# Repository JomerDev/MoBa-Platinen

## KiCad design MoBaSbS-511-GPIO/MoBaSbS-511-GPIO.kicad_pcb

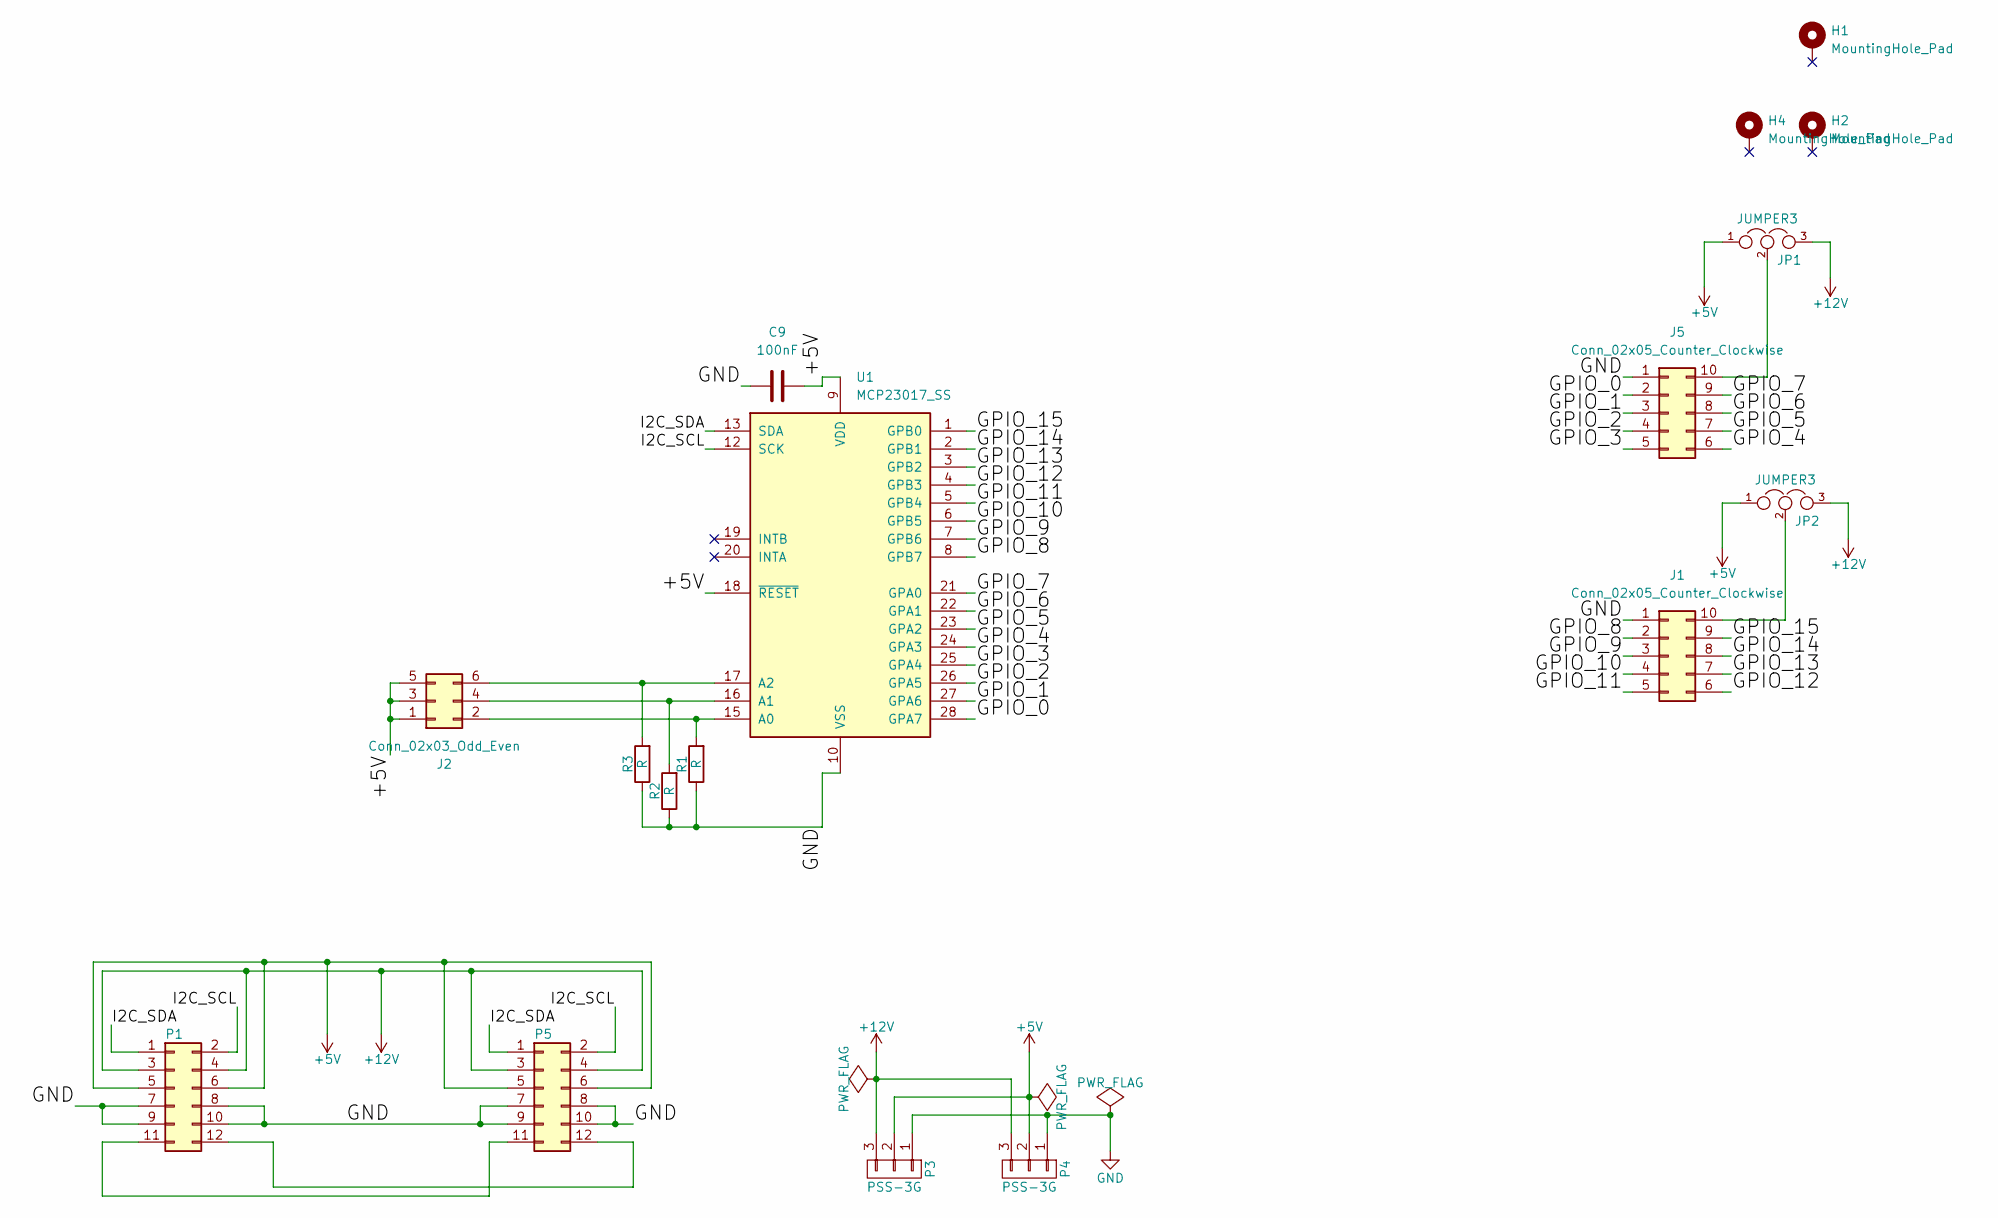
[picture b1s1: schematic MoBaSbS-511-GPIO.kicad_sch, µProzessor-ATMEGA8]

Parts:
C9: 100nF; C_0603_1608Metric
H1, H2, H4: MountingHole_Pad; MountingHole_2.7mm_M2.5_DIN965_Pad
J1, J5: Conn_02x05_Counter_Clockwise; IDC-Header_2x05_P2.54mm_Vertical
J2: Conn_02x03_Odd_Even; PinHeader_2x03_P2.54mm_Vertical
JP1, JP2: JUMPER3; Pin_Header_Straight_1x03
P1: 2x5_Buchse; PinSocket_2x06_P2.54mm_Horizontal
P3, P4: PSS-3G; PSS254-3G
P5: 2x5_Buchse; PinHeader_2x06_P2.54mm_Horizontal
R1, R2, R3: R; R_0603_1608Metric_Pad0.98x0.95mm_HandSolder
U1: MCP23017_SS; SSOP-28_5.3x10.2mm_P0.65mm

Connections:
+5V: C9.2, J2.1, J2.3, J2.5, JP1.1, JP2.1, P1.5, P1.6, P3.2, P4.2, P5.5, P5.6, U1.9 (VDD), U1.18 (~RESET)
+12V: JP1.3, JP2.3, P1.3, P1.4, P3.3, P4.3, P5.3, P5.4
/GPIO_0: J5.2, U1.28 (GPA7)
/GPIO_1: J5.3, U1.27 (GPA6)
/GPIO_2: J5.4, U1.26 (GPA5)
/GPIO_3: J5.5, U1.25 (GPA4)
/GPIO_4: J5.6, U1.24 (GPA3)
/GPIO_5: J5.7, U1.23 (GPA2)
/GPIO_6: J5.8, U1.22 (GPA1)
/GPIO_7: J5.9, U1.21 (GPA0)
/GPIO_8: J1.2, U1.8 (GPB7)
/GPIO_9: J1.3, U1.7 (GPB6)
/GPIO_10: J1.4, U1.6 (GPB5)
/GPIO_11: J1.5, U1.5 (GPB4)
/GPIO_12: J1.6, U1.4 (GPB3)
/GPIO_13: J1.7, U1.3 (GPB2)
/GPIO_14: J1.8, U1.2 (GPB1)
/GPIO_15: J1.9, U1.1 (GPB0)
/I2C_SCL: P1.2, P5.2, U1.12 (SCK)
/I2C_SDA: P1.1, P5.1, U1.13 (SDA)
GND: C9.1, J1.1, J5.1, P1.7, P1.8, P1.9, P1.10, P3.1, P4.1, P5.7, P5.8, P5.9, P5.10, R1.1, R2.1, R3.1, U1.10 (VSS)
unnamed: J1.10, JP2.2
unnamed: J2.2, R1.2, U1.15 (A0)
unnamed: J2.4, R2.2, U1.16 (A1)
unnamed: J2.6, R3.2, U1.17 (A2)
unnamed: J5.10, JP1.2
unnamed: P1.11, P5.11
unnamed: P1.12, P5.12

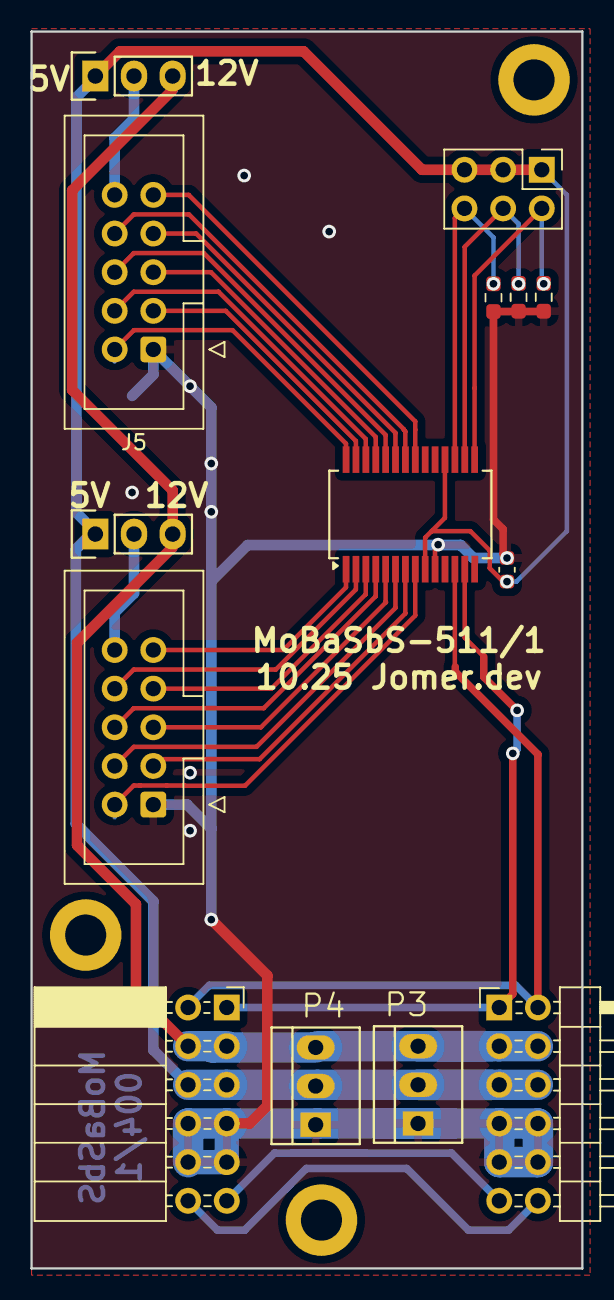
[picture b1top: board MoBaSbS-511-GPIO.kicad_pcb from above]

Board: 2 copper layers, 36.2 x 81.3 mm, 17 parts (0 on the bottom side), 28 nets.

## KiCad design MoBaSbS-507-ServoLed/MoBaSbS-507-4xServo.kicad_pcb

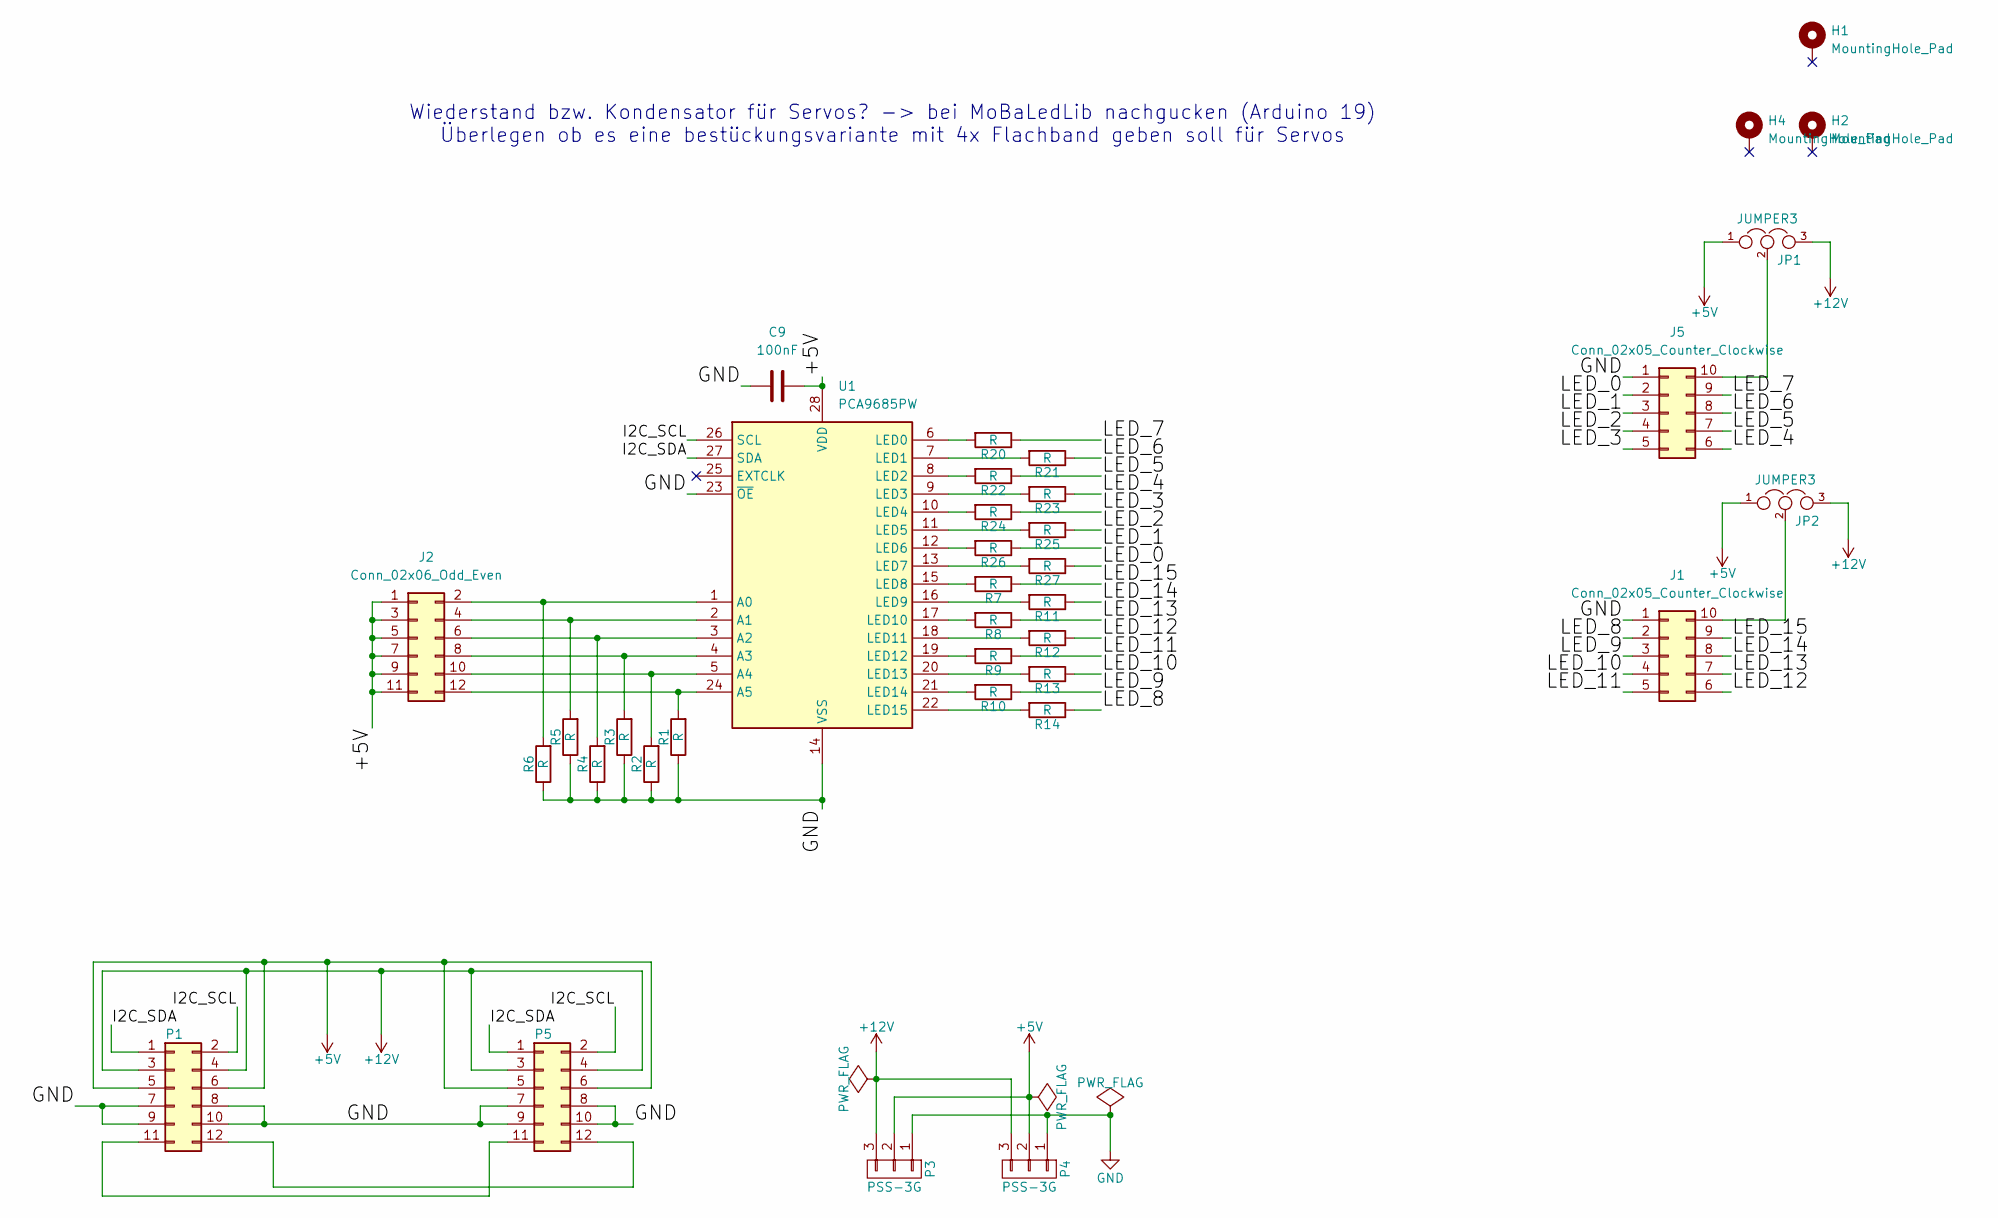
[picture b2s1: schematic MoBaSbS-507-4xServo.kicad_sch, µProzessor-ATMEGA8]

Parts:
C9: 100nF; C_0603_1608Metric
H1, H2, H4: MountingHole_Pad; MountingHole_2.7mm_M2.5_DIN965_Pad
J1, J5: Conn_02x05_Counter_Clockwise; IDC-Header_2x05_P2.54mm_Vertical
J2: Conn_02x06_Odd_Even; PinHeader_2x06_P2.54mm_Vertical
JP1, JP2: JUMPER3; Pin_Header_Straight_1x03
P1: 2x5_Buchse; PinSocket_2x06_P2.54mm_Horizontal
P3, P4: PSS-3G; PSS254-3G
P5: 2x5_Buchse; PinHeader_2x06_P2.54mm_Horizontal
R1, R2, R3, R4, R5, R6: R; R_0603_1608Metric_Pad0.98x0.95mm_HandSolder
R7, R8, R9, R10, R11, R12, R13, R14, R20, R21, R22, R23, R24, R25, R26, R27: R; R_1206_3216Metric_Pad1.30x1.75mm_HandSolder
U1: PCA9685PW; TSSOP-28_4.4x9.7mm_P0.65mm

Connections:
+5V: C9.2, J2.1, J2.3, J2.5, J2.7, J2.9, J2.11, JP1.1, JP2.1, P1.5, P1.6, P3.2, P4.2, P5.5, P5.6, U1.28 (VDD)
+12V: JP1.3, JP2.3, P1.3, P1.4, P3.3, P4.3, P5.3, P5.4
/I2C_SCL: P1.2, P5.2, U1.26 (SCL)
/I2C_SDA: P1.1, P5.1, U1.27 (SDA)
/LED_0: J5.2, R27.1
/LED_1: J5.3, R26.1
/LED_2: J5.4, R25.1
/LED_3: J5.5, R24.1
/LED_4: J5.6, R23.1
/LED_5: J5.7, R22.1
/LED_6: J5.8, R21.1
/LED_7: J5.9, R20.1
/LED_8: J1.2, R14.1
/LED_9: J1.3, R10.1
/LED_10: J1.4, R13.1
/LED_11: J1.5, R9.1
/LED_12: J1.6, R12.1
/LED_13: J1.7, R8.1
/LED_14: J1.8, R11.1
/LED_15: J1.9, R7.1
GND: C9.1, J1.1, J5.1, P1.7, P1.8, P1.9, P1.10, P3.1, P4.1, P5.7, P5.8, P5.9, P5.10, R1.1, R2.1, R3.1, R4.1, R5.1, R6.1, U1.14 (VSS), U1.23 (~OE)
unnamed: J1.10, JP2.2
unnamed: J2.2, R6.2, U1.1 (A0)
unnamed: J2.4, R5.2, U1.2 (A1)
unnamed: J2.6, R4.2, U1.3 (A2)
unnamed: J2.8, R3.2, U1.4 (A3)
unnamed: J2.10, R2.2, U1.5 (A4)
unnamed: J2.12, R1.2, U1.24 (A5)
unnamed: J5.10, JP1.2
unnamed: P1.11, P5.11
unnamed: P1.12, P5.12
unnamed: R20.2, U1.6 (LED0)
unnamed: R21.2, U1.7 (LED1)
unnamed: R22.2, U1.8 (LED2)
unnamed: R23.2, U1.9 (LED3)
unnamed: R24.2, U1.10 (LED4)
unnamed: R25.2, U1.11 (LED5)
unnamed: R26.2, U1.12 (LED6)
unnamed: R27.2, U1.13 (LED7)
unnamed: R7.2, U1.15 (LED8)
unnamed: R11.2, U1.16 (LED9)
unnamed: R8.2, U1.17 (LED10)
unnamed: R12.2, U1.18 (LED11)
unnamed: R9.2, U1.19 (LED12)
unnamed: R13.2, U1.20 (LED13)
unnamed: R10.2, U1.21 (LED14)
unnamed: R14.2, U1.22 (LED15)

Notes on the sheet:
Wiederstand bzw. Kondensator für Servos? -> bei MoBaLedLib nachgucken (Arduino 19) Überlegen ob es eine bestückungsvariante mit 4x Flachband geben soll für Servos

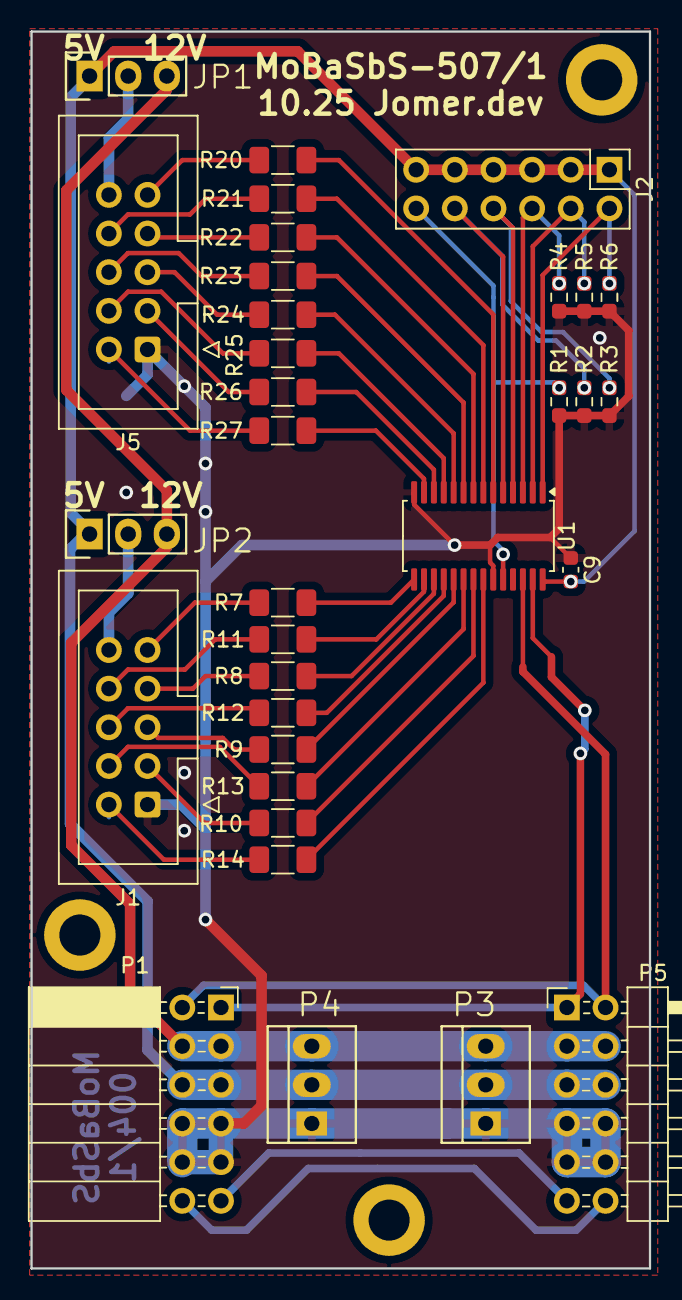
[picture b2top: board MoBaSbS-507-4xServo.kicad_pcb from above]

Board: 2 copper layers, 40.6 x 81.3 mm, 36 parts (0 on the bottom side), 47 nets.

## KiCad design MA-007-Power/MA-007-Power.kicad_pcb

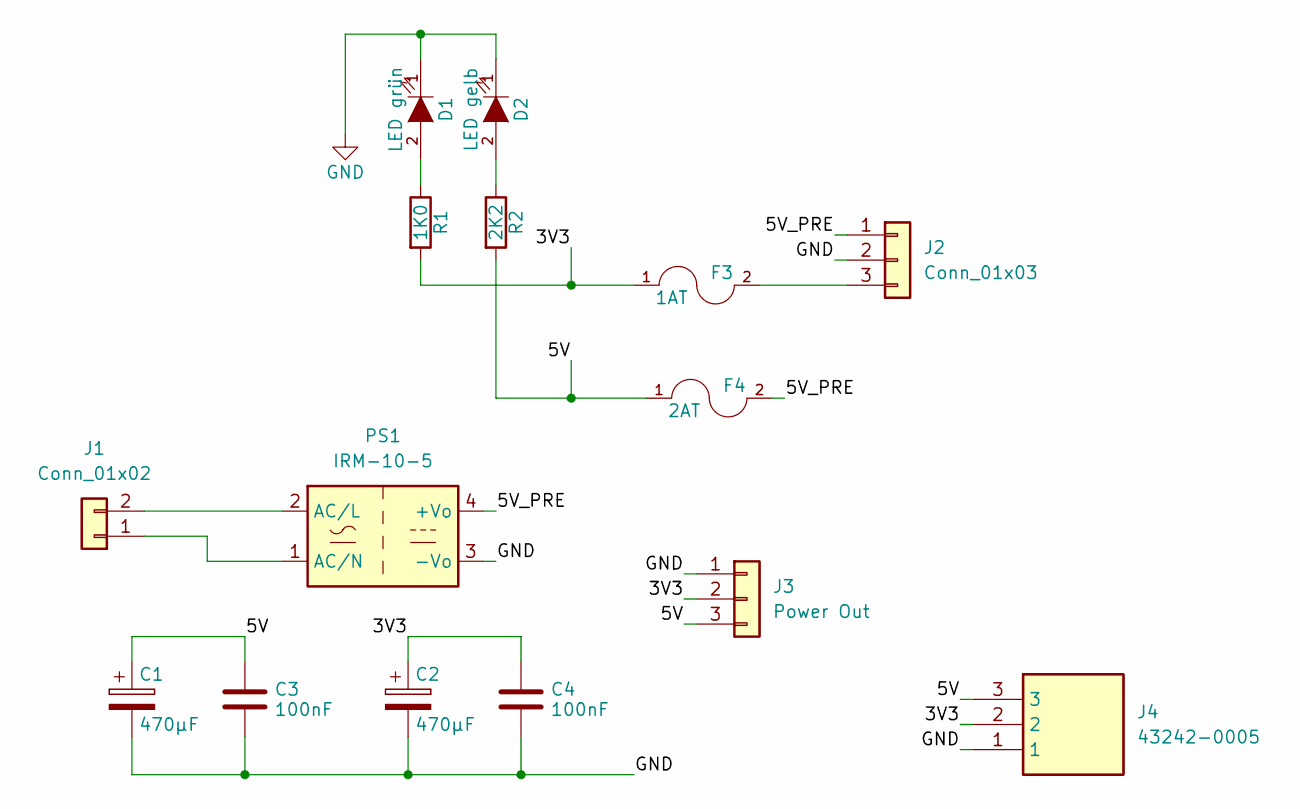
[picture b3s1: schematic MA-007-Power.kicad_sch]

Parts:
C1, C2: 470µF; CP_Radial_D8.0mm_P5.00mm
C3, C4: 100nF; C_1206_3216Metric
D1: LED grün; LED_1206_3216Metric
D2: LED gelb; LED_1206_3216Metric
F3: 1AT; Fuseholder_Littelfuse_Nano2_154x
F4: 2AT; Fuseholder_Littelfuse_Nano2_154x
J1: Conn_01x02; PhoenixContact_MSTBVA_2,5_2-G_1x02_P5.00mm_Vertical
J2: Conn_01x03; PinSocket_1x03_P2.54mm_Vertical
J3: Power Out; Molex_KK-254_AE-6410-03A_1x03_P2.54mm_Vertical
J4: 43242-0005; Molex_MiniFitJr_1x3_PCB; Mouser Part Number 538-43242-0005
PS1: IRM-10-5; Converter_ACDC_MeanWell_IRM-10-xx_THT
R1: 1K0; R_1206_3216Metric
R2: 2K2; R_1206_3216Metric

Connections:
/3V3: C2.1, C4.1, F3.1, J3.2, J4.2, R1.2
/5V: C1.1, C3.1, F4.1, J3.3, J4.3, R2.2
/5V_PRE: F4.2, J2.1, PS1.4 (+Vo)
GND: C1.2, C2.2, C3.2, C4.2, D1.1 (K), D2.1 (K), J2.2, J3.1, J4.1, PS1.3 (-Vo)
unnamed: D1.2 (A), R1.1
unnamed: D2.2 (A), R2.1
unnamed: J1.1, PS1.1 (AC/N)
unnamed: J1.2, PS1.2 (AC/L)
unnamed: F3.2, J2.3

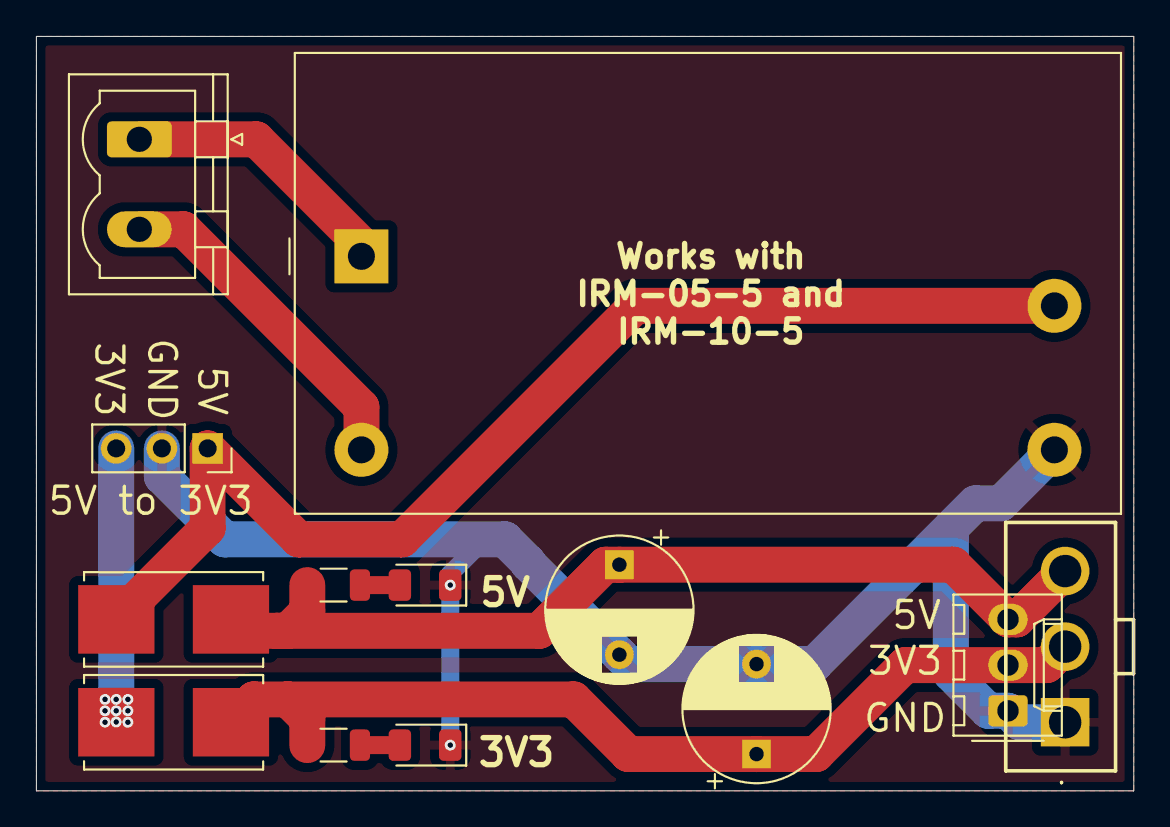
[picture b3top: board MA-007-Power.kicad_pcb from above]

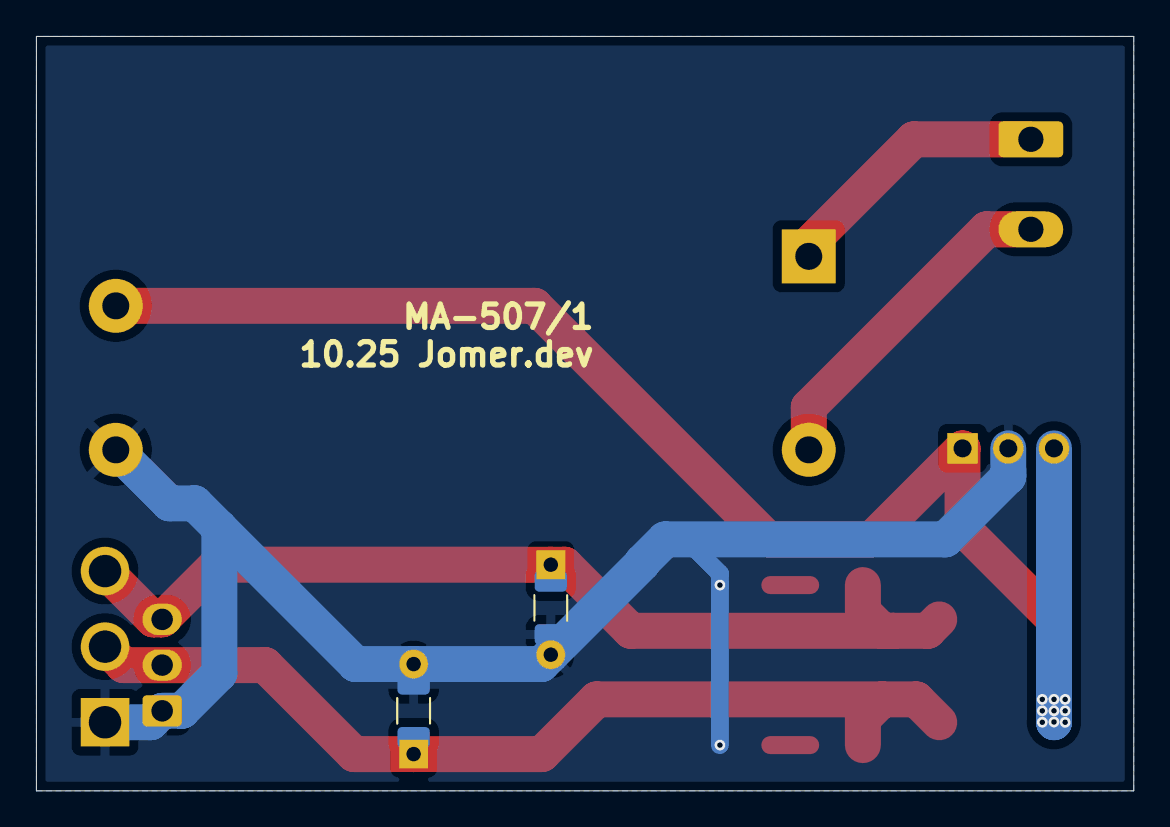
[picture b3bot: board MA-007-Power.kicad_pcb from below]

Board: 2 copper layers, 61.0 x 41.9 mm, 15 parts (2 on the bottom side), 9 nets.

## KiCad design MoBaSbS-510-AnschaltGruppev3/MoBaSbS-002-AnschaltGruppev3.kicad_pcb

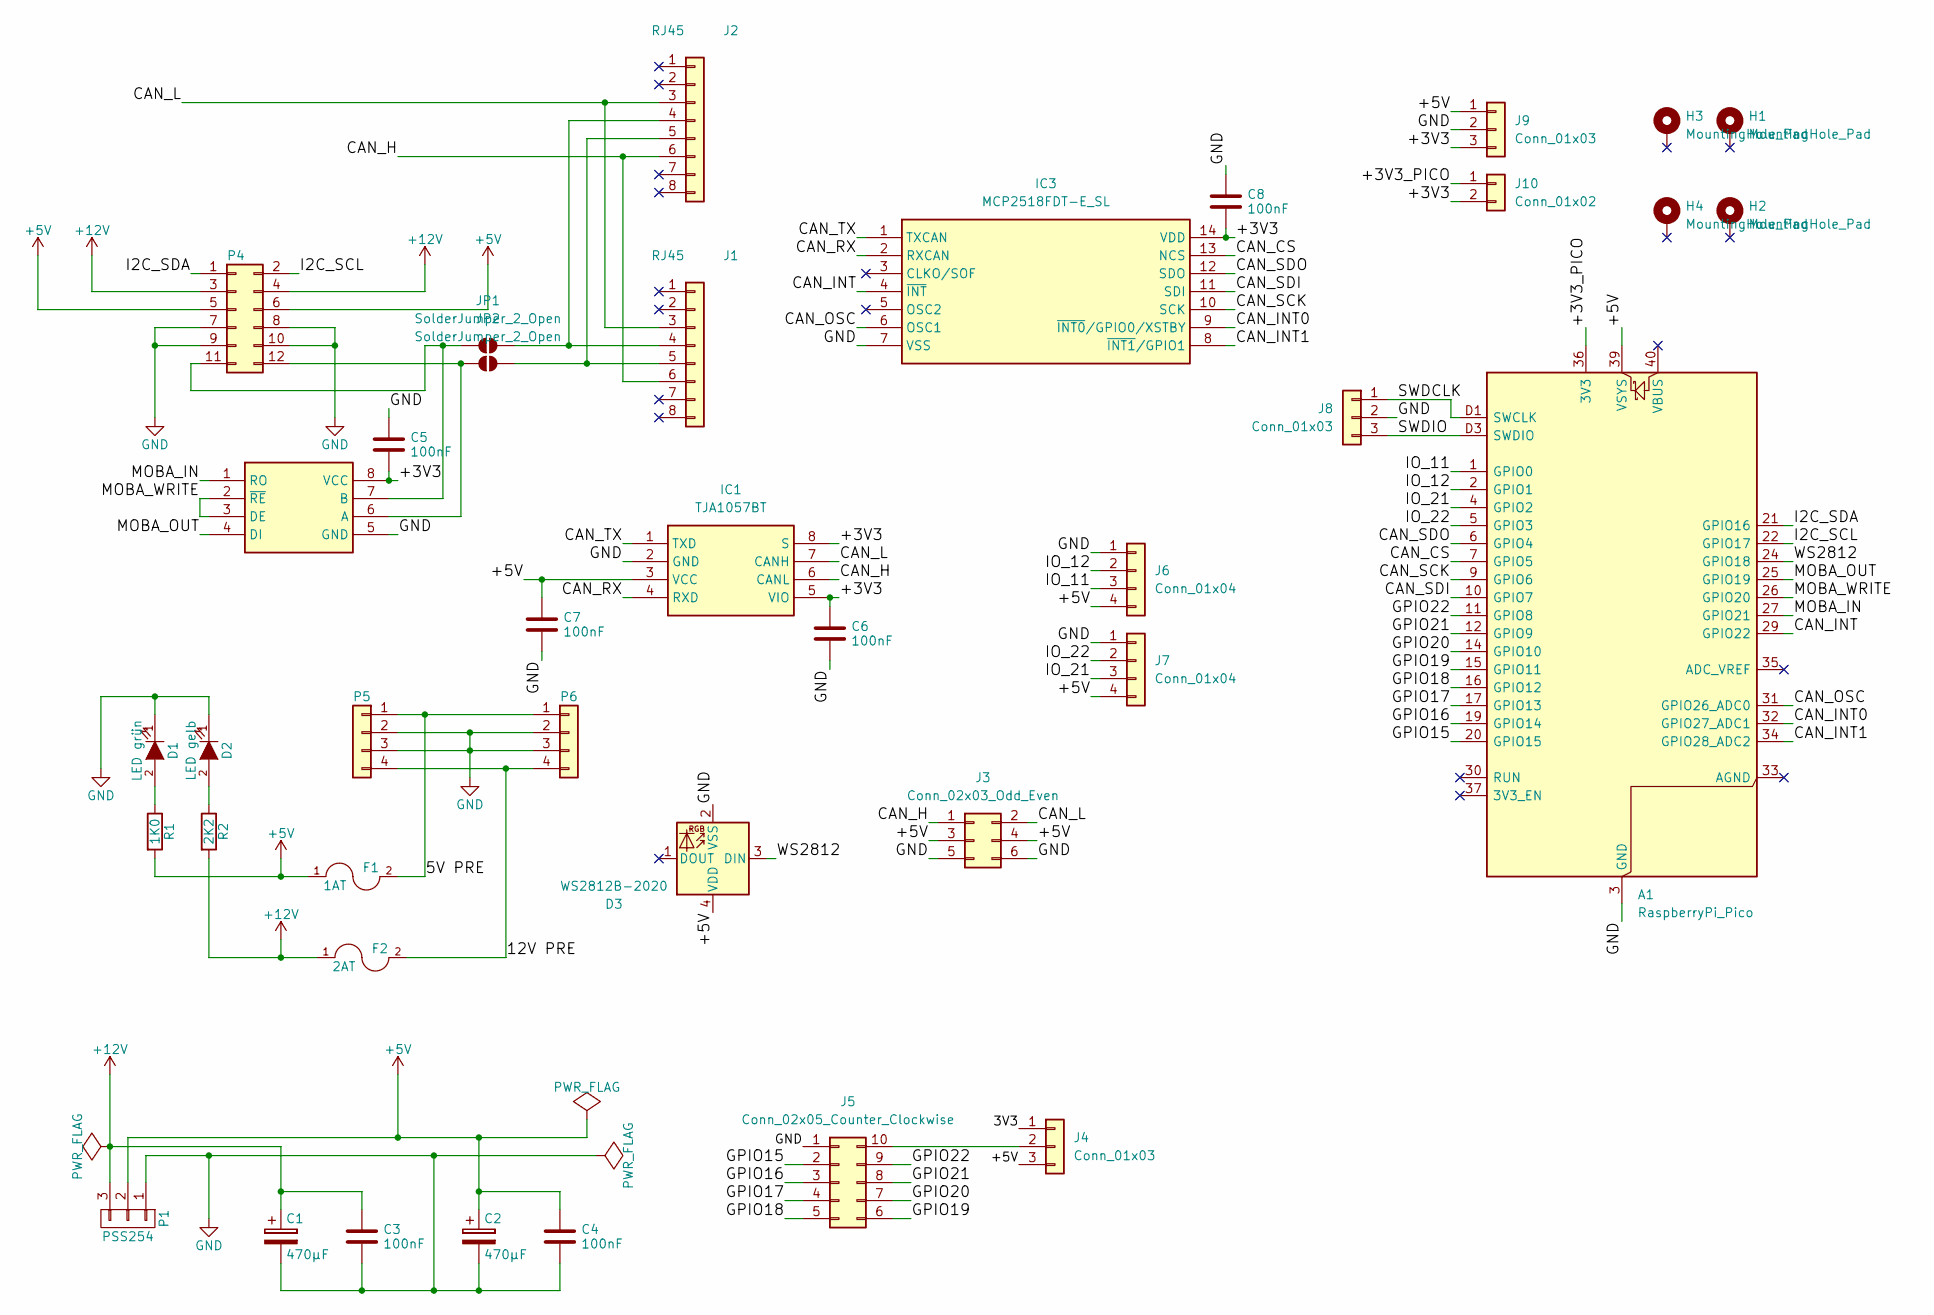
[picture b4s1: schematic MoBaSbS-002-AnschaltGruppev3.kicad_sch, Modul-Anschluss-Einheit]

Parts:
A1: RaspberryPi_Pico; RaspberryPi_Pico_Original_SMD_HandSolder
C1, C2: 470µF; CP_Radial_D8.0mm_P5.00mm
C3, C4: 100nF; C_1206_3216Metric
C5, C6, C7, C8: 100nF; C_0603_1608Metric
D1: LED grün; LED_1206_3216Metric
D2: LED gelb; LED_1206_3216Metric
D3: WS2812B-2020; LED_WS2812B-Mini_PLCC4_3.5x3.5mm
F1: 1AT; Fuseholder_Littelfuse_Nano2_154x
F2: 2AT; Fuseholder_Littelfuse_Nano2_154x
H1, H2, H3, H4: MountingHole_Pad; MountingHole_2.7mm_M2.5_DIN965_Pad
IC1: TJA1057BT; SOIC127P600X175-8N; Manufacturer_Part_Number TJA1057BT
IC2: SP3485EN-L_TR; SOIC127P600X175-8N; Mouser Part Number 701-SP3485EN-L/TR
IC3: MCP2518FDT-E_SL; SOIC127P600X175-14N; Mouser Part Number 579-MCP2518FDT-E/SL
J1, J2: RJ45; RJ45_8
J3: Conn_02x03_Odd_Even; PinSocket_2x03_P2.54mm_Horizontal
J4, J8: Conn_01x03; PinHeader_1x03_P2.54mm_Vertical
J5: Conn_02x05_Counter_Clockwise; IDC-Header_2x05_P2.54mm_Vertical
J6, J7: Conn_01x04; Molex_KK-254_AE-6410-04A_1x04_P2.54mm_Vertical
J9: Conn_01x03; PinHeader_1x03_P2.54mm_Vertical_SMD_Pin1Left
J10: Conn_01x02; PinHeader_1x02_P2.54mm_Vertical_SMD_Pin1Left
JP1, JP2: SolderJumper_2_Open; SolderJumper-2_P1.3mm_Open_RoundedPad1.0x1.5mm
P1: PSS254; Molex_KK-254_AE-6410-03A_1x03_P2.54mm_Vertical
P4: 2x5_Buchse; PinSocket_2x06_P2.54mm_Horizontal
P5, P6: Wago; CONN_5566-04A_MOL
R1: 1K0; R_1206_3216Metric
R2: 2K2; R_1206_3216Metric

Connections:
+5V: A1.39 (VSYS), C2.1, C4.1, C7.1, D3.4 (VDD), F1.1, IC1.3 (VCC), J3.3, J3.4, J4.3, J6.4, J7.4, J9.1, P1.2, P4.5, P4.6, R1.2
+12V: C1.1, C3.1, F2.1, P1.3, P4.3, P4.4, R2.2
/3V3: J4.1
/5V PRE: F1.2, P5.1, P6.1
/12V PRE: F2.2, P5.4, P6.4
/+3V3: C5.2, C6.1, C8.2, IC1.5 (VIO), IC1.8 (S), IC2.8 (VCC), IC3.14 (VDD), J9.3, J10.2
/+3V3_PICO: A1.36 (3V3), J10.1
/CAN_CS: A1.7 (GPIO5), IC3.13 (NCS)
/CAN_H: IC1.6 (CANL), J1.6, J2.6, J3.1
/CAN_INT: A1.29 (GPIO22), IC3.4 (~INT)
/CAN_INT0: A1.32 (GPIO27_ADC1), IC3.9 (~INT0/GPIO0/XSTBY)
/CAN_INT1: A1.34 (GPIO28_ADC2), IC3.8 (~INT1/GPIO1)
/CAN_L: IC1.7 (CANH), J1.3, J2.3, J3.2
/CAN_OSC: A1.31 (GPIO26_ADC0), IC3.6 (OSC1)
/CAN_RX: IC1.4 (RXD), IC3.2 (RXCAN)
/CAN_SCK: A1.9 (GPIO6), IC3.10 (SCK)
/CAN_SDI: A1.10 (GPIO7), IC3.11 (SDI)
/CAN_SDO: A1.6 (GPIO4), IC3.12 (SDO)
/CAN_TX: IC1.1 (TXD), IC3.1 (TXCAN)
/GPIO15: A1.20 (GPIO15), J5.2
/GPIO16: A1.19 (GPIO14), J5.3
/GPIO17: A1.17 (GPIO13), J5.4
/GPIO18: A1.16 (GPIO12), J5.5
/GPIO19: A1.15 (GPIO11), J5.6
/GPIO20: A1.14 (GPIO10), J5.7
/GPIO21: A1.12 (GPIO9), J5.8
/GPIO22: A1.11 (GPIO8), J5.9
/I2C_SCL: A1.22 (GPIO17), P4.2
/I2C_SDA: A1.21 (GPIO16), P4.1
/IO_11: A1.1 (GPIO0), J6.3
/IO_12: A1.2 (GPIO1), J6.2
/IO_21: A1.4 (GPIO2), J7.3
/IO_22: A1.5 (GPIO3), J7.2
/MOBA_IN: A1.27 (GPIO21), IC2.1 (RO)
/MOBA_OUT: A1.25 (GPIO19), IC2.4 (DI)
/MOBA_WRITE: A1.26 (GPIO20), IC2.2 (~RE), IC2.3 (DE)
/SWDCLK: A1.D1 (SWCLK), J8.1
/SWDIO: A1.D3 (SWDIO), J8.3
/WS2812: A1.24 (GPIO18), D3.3 (DIN)
GND: A1.3 (GND), A1.8 (GND), A1.13 (GND), A1.18 (GND), A1.23 (GND), A1.28 (GND), A1.38 (GND), A1.D2 (GND), C1.2, C2.2, C3.2, C4.2, C5.1, C6.2, C7.2, C8.1, D1.1 (K), D2.1 (K), D3.2 (VSS), IC1.2 (GND), IC2.5 (GND), IC3.7 (VSS), J3.5, J3.6, J5.1, J6.1, J7.1, J8.2, J9.2, P1.1, P4.7, P4.8, P4.9, P4.10, P5.2, P5.3, P6.2, P6.3
unnamed: D1.2 (A), R1.1
unnamed: D2.2 (A), R2.1
unnamed: IC2.6 (A), JP2.1 (A), P4.12
unnamed: IC2.7 (B), JP1.1 (A), P4.11
unnamed: J1.4, J2.4, JP1.2 (B)
unnamed: J1.5, J2.5, JP2.2 (B)
unnamed: J4.2, J5.10

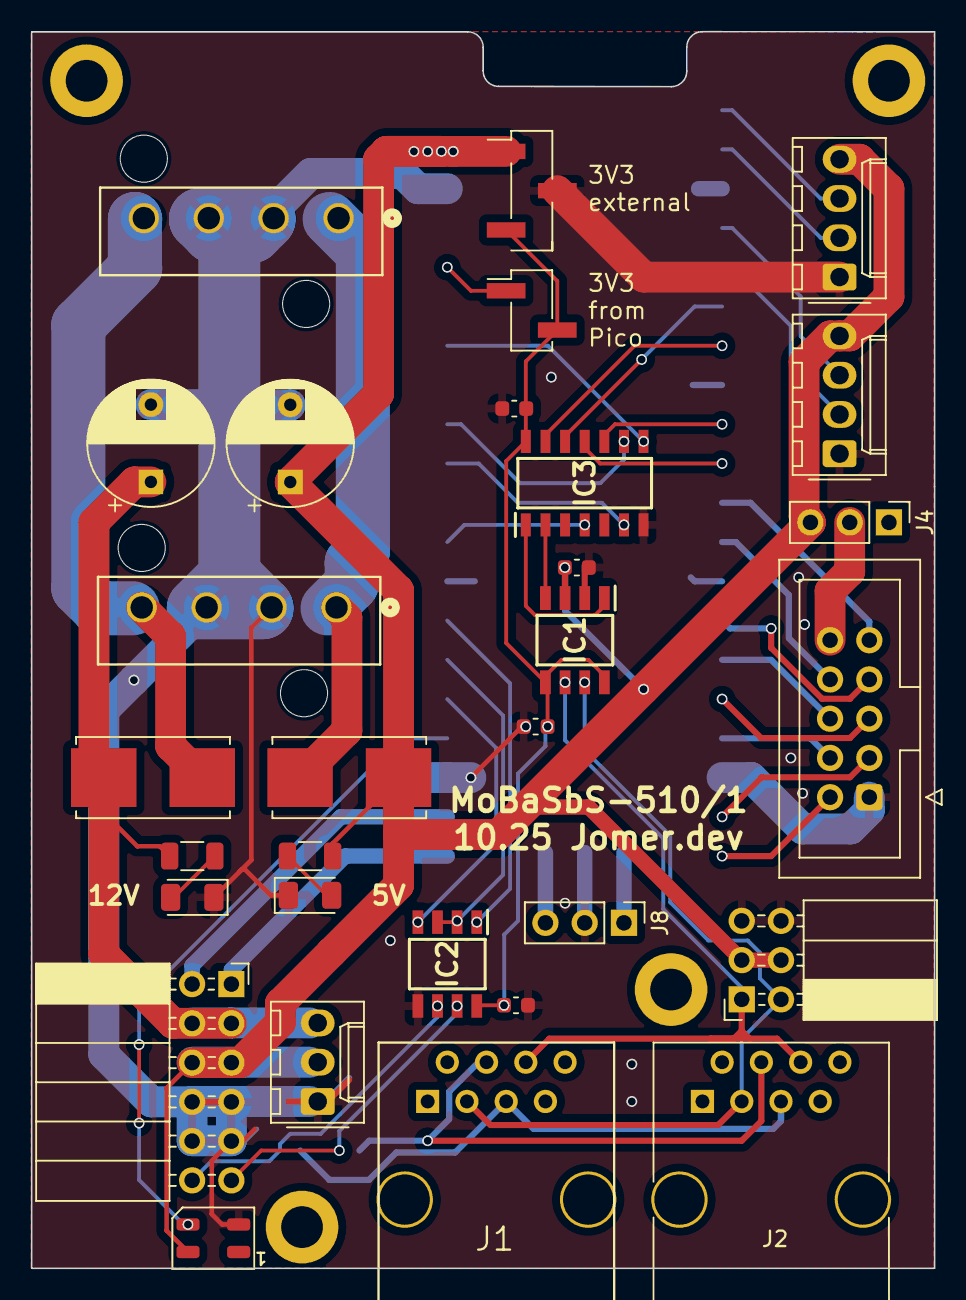
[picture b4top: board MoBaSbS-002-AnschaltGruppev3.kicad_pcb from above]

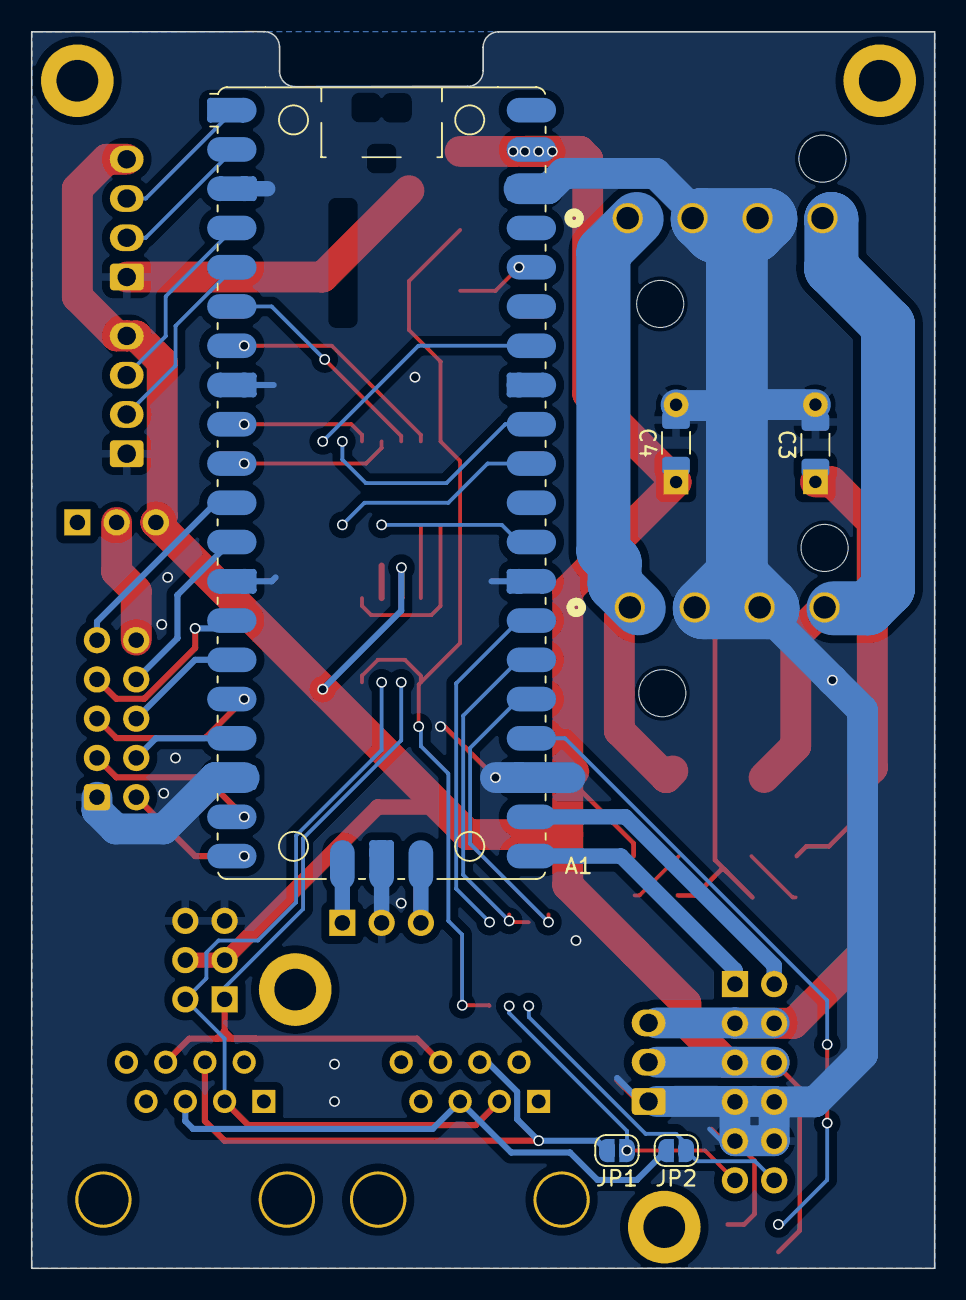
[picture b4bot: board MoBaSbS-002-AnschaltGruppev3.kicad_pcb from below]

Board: 2 copper layers, 58.4 x 80.0 mm, 39 parts (5 on the bottom side), 46 nets.

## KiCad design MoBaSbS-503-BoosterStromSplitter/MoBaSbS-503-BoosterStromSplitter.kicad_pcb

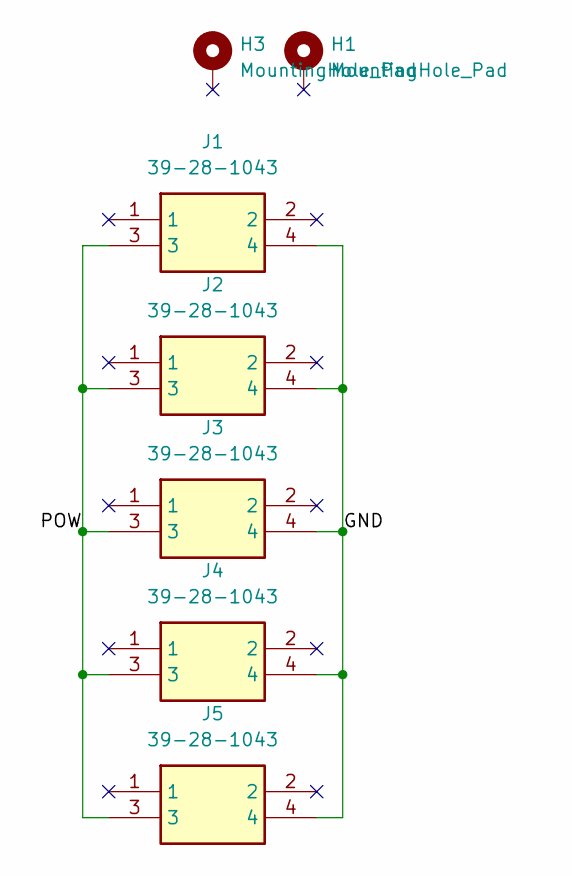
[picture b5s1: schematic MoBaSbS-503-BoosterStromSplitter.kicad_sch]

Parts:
H1, H3: MountingHole_Pad; MountingHole_2.7mm_M2.5_DIN965_Pad
J1, J2, J3, J4, J5: 39-28-1043; Molex_MiniFitJr_2x2_PCB; Mouser Part Number 538-39-28-1043

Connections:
/GND: J1.4, J2.4, J3.4, J4.4, J5.4
/POW: J1.3, J2.3, J3.3, J4.3, J5.3

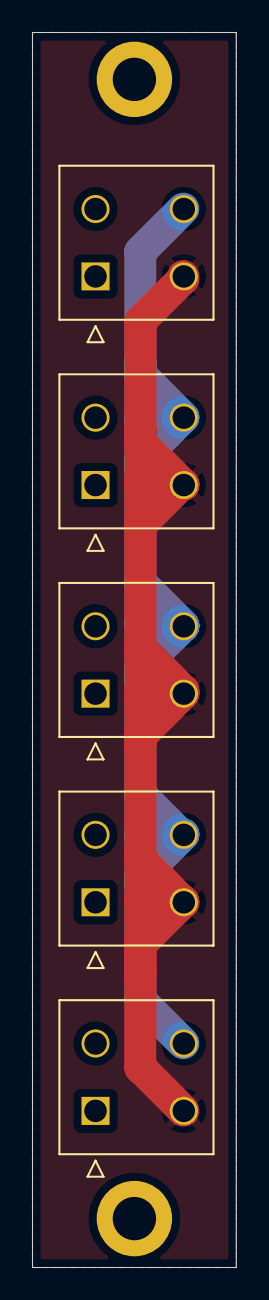
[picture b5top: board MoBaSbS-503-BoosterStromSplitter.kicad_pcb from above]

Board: 2 copper layers, 12.7 x 77.0 mm, 7 parts (0 on the bottom side), 2 nets.

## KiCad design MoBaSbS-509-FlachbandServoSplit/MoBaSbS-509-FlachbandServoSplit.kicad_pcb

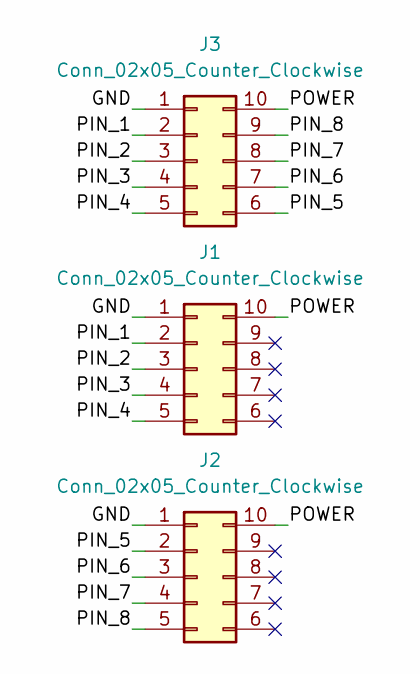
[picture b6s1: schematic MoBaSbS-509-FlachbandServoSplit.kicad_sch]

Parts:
J1, J2: Conn_02x05_Counter_Clockwise; IDC-Header_2x05_P2.54mm_Vertical
J3: Conn_02x05_Counter_Clockwise; IDC-Header_2x05_P2.54mm_Horizontal

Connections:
/GND: J1.1, J2.1, J3.1
/PIN_1: J1.2, J3.2
/PIN_2: J1.3, J3.3
/PIN_3: J1.4, J3.4
/PIN_4: J1.5, J3.5
/PIN_5: J2.2, J3.6
/PIN_6: J2.3, J3.7
/PIN_7: J2.4, J3.8
/PIN_8: J2.5, J3.9
/POWER: J1.10, J2.10, J3.10

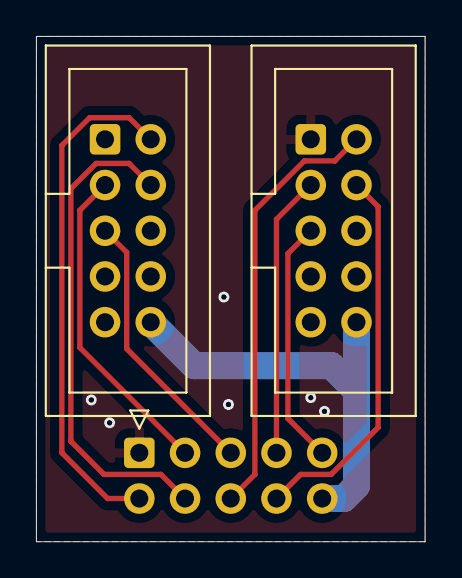
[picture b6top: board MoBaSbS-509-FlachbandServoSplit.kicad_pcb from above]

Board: 2 copper layers, 21.6 x 28.1 mm, 3 parts (0 on the bottom side), 10 nets.
